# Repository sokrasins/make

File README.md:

# Make Roanoke Work

## Organization

- `bring_up`: Instructions and resources for BeepBeep bring-up (after assembly)
- `card_test`: micropython test code to verify wiegand interpretation
- `docs`: Relevant documents, photos, images, etc. 
- `wiegand_sig_gen`: RP2040-based wiegand signal generator
- `cheepcheep`: A C-based rewrite of the beepbeep firmware

## Set up

Any binary files are tracked via git-lfs. To access:

1. Install git-lfs:

```
sudo apt install git-lfs
git lfs install
```

2. Pull the lfs objects:

```
git lfs pull
```

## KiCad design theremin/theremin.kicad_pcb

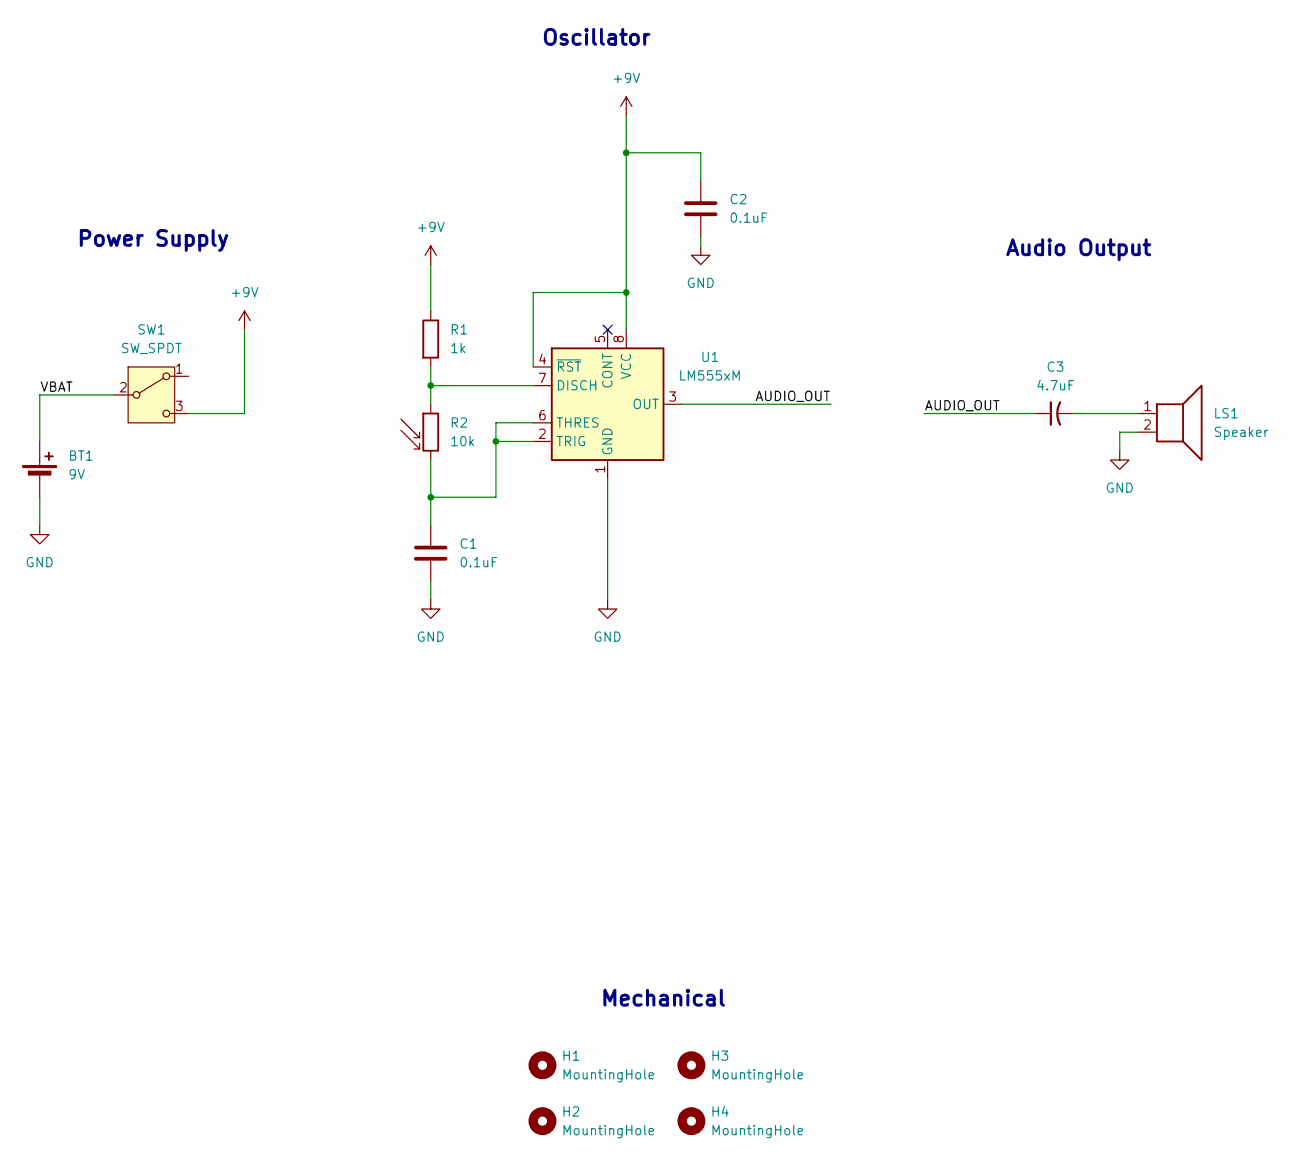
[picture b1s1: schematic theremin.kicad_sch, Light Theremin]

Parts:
BT1: 9V; PinHeader_1x02_P2.54mm_Vertical
C1, C2: 0.1uF; C_Rect_L4.0mm_W2.5mm_P2.50mm
C3: 4.7uF; CP_Radial_D5.0mm_P2.50mm
H1, H2, H3, H4: MountingHole; MountingHole_3.2mm_M3
LS1: Speaker; PinHeader_1x02_P2.54mm_Vertical
R1: 1k; R_Axial_DIN0207_L6.3mm_D2.5mm_P10.16mm_Horizontal
R2: 10k; R_LDR_4.9x4.2mm_P2.54mm_Vertical
SW1: SW_SPDT; SW_E-Switch_EG1224_SPDT_Angled
U1: LM555xM; SOIC-8_3.9x4.9mm_P1.27mm

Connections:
+9V: C2.1, R1.1, SW1.3 (C), U1.4 (~RST), U1.8 (VCC)
/AUDIO_OUT: C3.1, U1.3 (OUT)
/VBAT: BT1.1 (+), SW1.2 (B)
GND: BT1.2 (-), C1.2, C2.2, LS1.2, U1.1 (GND)
unnamed: C3.2, LS1.1
unnamed: R1.2, R2.1, U1.7 (DISCH)
unnamed: C1.1, R2.2, U1.2 (TRIG), U1.6 (THRES)

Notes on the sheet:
Mechanical
Oscillator
Audio Output
Power Supply

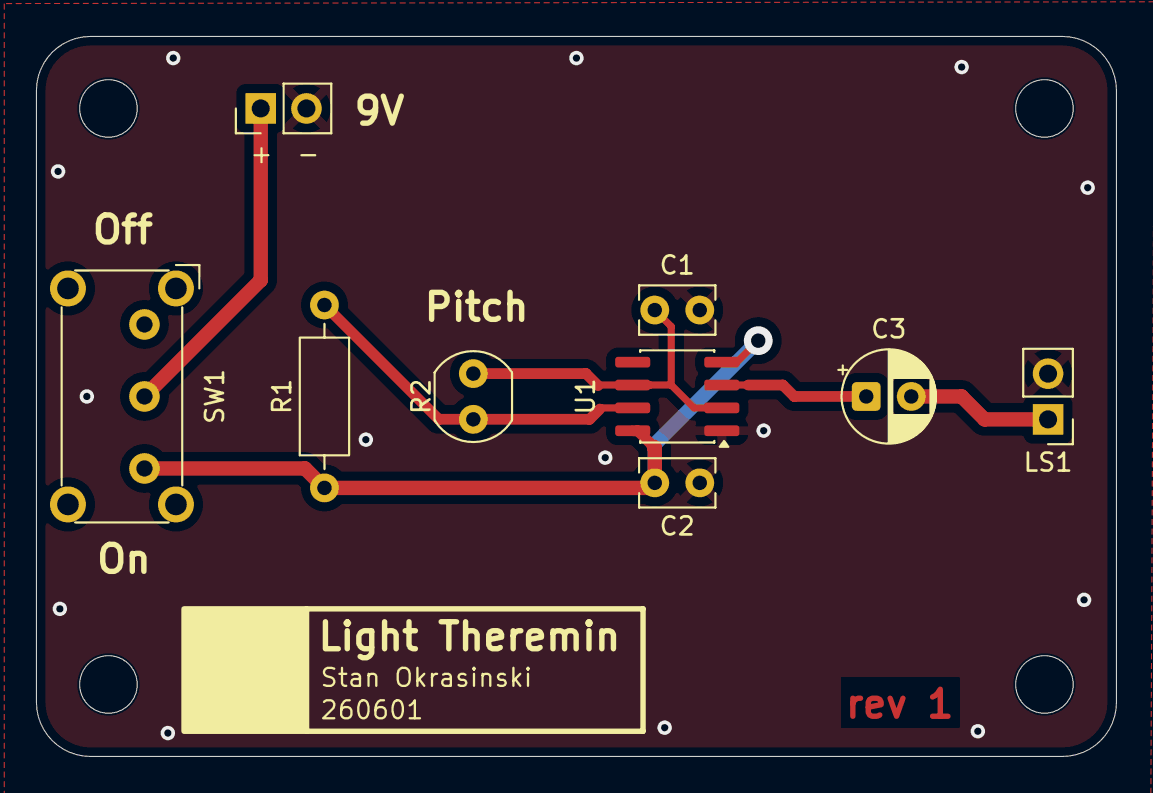
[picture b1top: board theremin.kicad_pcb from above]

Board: 2 copper layers, 60.0 x 40.0 mm, 13 parts (0 on the bottom side), 7 nets.

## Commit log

2025-06-12 move bin file over to lfs
2025-06-14 Add beepbeep submodule
2025-06-16 add test firmware
2025-06-17 Added wiegand emulator for rpi pico
2025-06-17 Add repeat command, fix parsing bug
2025-06-17 hex input for send now
2025-06-19 Working against test now, added readme
2025-06-19 Rename stuff"
2025-06-19 rename, add readme
2025-06-19 update names
2025-06-19 readme
2025-06-19 Fix bad table formatting
2025-06-19 Added photos and gitignore
2025-06-24 Add cheepcheep
2025-06-24 Clear warnings and add workspace
2025-06-25 Fix wiegand, add wifi
2025-06-27 Added websocket client
2025-06-27 no warnings, clean up client messaging
2025-06-27 storing authorized cards and checking against them
2025-06-28 proper hash check
2025-06-28 Service the other door and generic server reqs
2025-06-28 logging
2025-06-28 Update lockout
2025-06-29 Tweak defaults into a usable door
2025-06-29 Bump door task's stack up
2025-06-29 Flip door lock polarity
2025-06-29 some reliability changes
2025-06-29 Start some build instructions
2025-06-30 Added check for DFU
2025-06-30 bugfixing and cleanup
2025-06-30 push old work
2025-06-30 experimenting with ota
2025-06-30 Clean up DFU code
2025-07-01 Add attribution
2025-07-01 Verified working
2025-07-01 Add sys
2025-07-01 Adding console
2025-07-01 start accepting console commands for device config
2025-07-01 Try some new reconnection logic in the client
2025-07-02 Add default config settings
2025-07-02 Set default config value, implement more config handlers
2025-07-04 MOve cheepcheep
2026-06-01 add theremin board
2026-06-15 push local diff
2026-06-15 Added sch pdf
